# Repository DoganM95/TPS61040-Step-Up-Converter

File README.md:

# Intro

Step-Up converter module using TPS61040, ideal to boost a single li-ion cell (typically 2.5V - 4.2V) or a USB power supply (5V) to up to 28V, to power any device that does not need lots of current, but requires a very low quiescent current to ensure the battery is not drained, when there is no load.

## Specs of the IC

- 1.8V - 6V input
- 1.8V - 28V adj. output Voltage
- 0.4A output current
- 28uA quiescent current

## Specs of the PCB (measured)

- 2.2V - 6V input
- 2.2V - 28V adj. output
- 0.4A output
- 60 uA quiescent current

## Power Consumption 

Power consumed by the board alone with no load (quiescent current)

- 61 uA @ 6.0V in (6V out)
- 59 uA @ 5.0V in (6V out)
- 60 uA @ 4.2V in (6V out)
- 63 uA @ 3.3V in (6V out)
- 65 uA @ 3.0V in (6V out)
- 73 uA @ 2.2V in (6V out)

## Power Output

output range 2.93V - 13.87V  
output power @ 3.0V in  
V out without load -> V out with load after @  

- 13.87V loadless -> 13.8V @ 100mA  
- 12.00V loadless -> 11.8V @ 100 mA  
- 9.00V loadless -> 8.8V @ 100 mA  
- 6.0V loadless -> 5.8V @ 100mA  
- 5.0V loadless -> 4.7V @ 100mA  
- 3.3V loadless -> 3.0V @ 100mA  

## BOM

- `C_FF`: 0603 22pF
- `C_IN`: 0603 4.7uF
- `C_O`: 0603 1nF
- `D1`: any Schottky between SS14 & SS54
- `EN_J`: short, if board should be always on -> EN becomes redundant
- `L1`: CD43 10uH
- `R1`: 0603 up to 1MOhm, use if VR1 is unnecessary and needed resstance is known
- `R2`: 0603 100kOhm
- `U1`: SOT23-5 TPS61040
- `VR1`: 3x3 trimpot 1MOhm, sets output voltage by adjusting its resistance

## PCB

<table>
  <tr>
    <td>
      
    </td>
    <td>
      
    </td>
  </tr>
</table>

## Schematic

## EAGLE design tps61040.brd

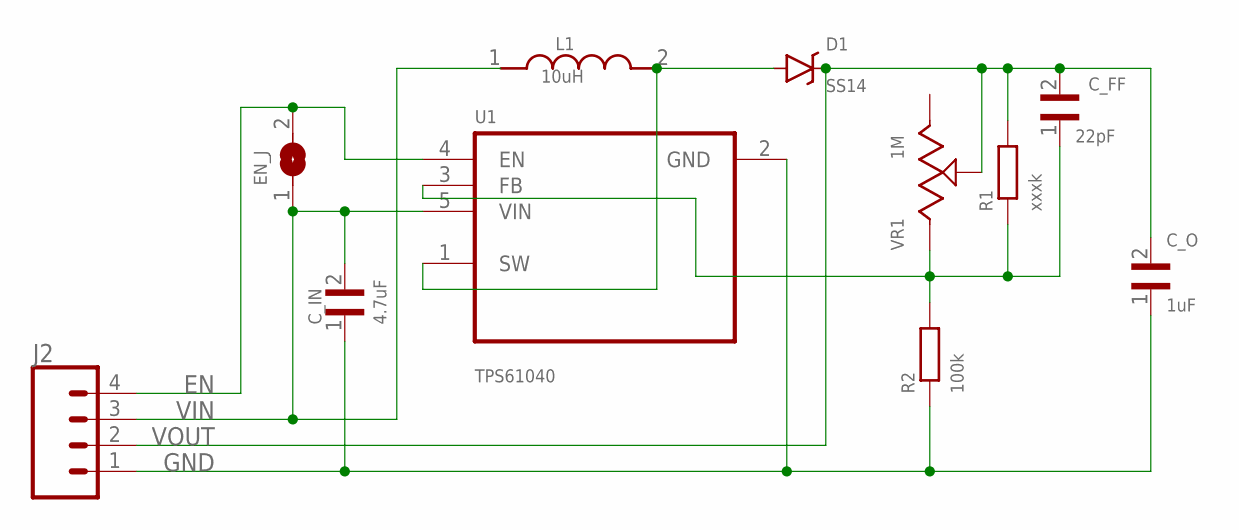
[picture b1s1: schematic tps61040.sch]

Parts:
C_FF: 22pF; WCAP-CSGP_0603_REFLOW
C_IN: 4.7uF; WCAP-CSGP_0603_REFLOW
C_O: 1uF; WCAP-CSGP_0603_REFLOW
D1: SS14; DO-214AC
EN_J: SJ
J2: CONN_041X04_NO_SILK; 1X04_NO_SILK
L1: 10uH; CD43
R1: xxxk; R0603
R2: 100k; R0603
U1: TPS61040; SOT95P280X145-5N
VR1: 1M; TRIMMER_TC33X-2-103G

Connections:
EN: EN_J.2, J2.4, U1.4 (EN)
GND: C_IN.1, C_O.1, J2.1, R2.1, U1.2 (GND)
unnamed: D1.A, L1.2, U1.1 (SW)
unnamed: C_FF.1, R1.1, R2.2, U1.3 (FB), VR1.1 (CCW)
VIN: C_IN.2, EN_J.1, J2.3, L1.1, U1.5 (VIN)
VOUT: C_FF.2, C_O.2, D1.C, J2.2, R1.2, VR1.2 (WIPER)

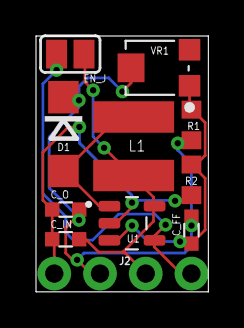
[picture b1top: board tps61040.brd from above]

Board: 2 copper layers, 9.6 x 14.2 mm, 11 parts (0 on the bottom side), 6 nets.

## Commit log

2024-04-21 init eagle project
2024-07-14 add schematic
2024-07-14 add pcb images
2024-07-14 implement v1
2024-07-14 switch to 0603 sized components
2024-07-16 [ImgBot] Optimize images
    *Total -- 133.30kb -> 41.35kb (68.98%)
    /assets/pcb-bottom_v1.png -- 52.56kb -> 16.11kb (69.34%)
    /assets/pcb_v1.png -- 80.74kb -> 25.24kb (68.74%)
2024-07-29 update some lib
2024-07-29 add images of v1.1
2024-07-29 add gerber of v1.1
2024-08-01 [ImgBot] Optimize images
    *Total -- 107.87kb -> 54.17kb (49.78%)
    /assets/pcb-bottom_v1.1.png -- 50.10kb -> 23.98kb (52.13%)
    /assets/pcb-top_v1.1.png -- 57.77kb -> 30.19kb (47.75%)
2024-12-23 Update qc with new resistors
2024-12-23 Create bom
2024-12-23 create release (gerber file)
2024-12-23 add images of pcb v1.2 and schematic
2024-12-23 fix assets
2024-12-23 [ImgBot] Optimize images
    *Total -- 329.61kb -> 114.32kb (65.32%)
    /assets/1.2-top.png -- 88.43kb -> 25.55kb (71.11%)
    /assets/1.2-bottom.png -- 82.73kb -> 24.79kb (70.03%)
    /assets/1.2_schematic.png -- 56.13kb -> 20.58kb (63.34%)
    /assets/1.1-bottom.png -- 44.67kb -> 18.75kb (58.03%)
    /assets/1.1-top.png -- 57.64kb -> 24.65kb (57.24%)
2024-12-23 add space for header plastic

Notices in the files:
parts and their libraries:
Passive_Capacitors_rev15a: Copyright: Würth Elektronik
SparkFun-Connectors: Licensing: Creative Commons ShareAlike 4.0 International - https://creativecommons.org/licenses/by-sa/4.0
